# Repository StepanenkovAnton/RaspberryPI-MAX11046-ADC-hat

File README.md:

# RaspberryPI-MAX11046-ADC-hat
The Raspberry PI add-on boad with the 16 bit 6-channel ADC intended for 3 voltage + 3 current channels high-speed sampling in order to measure the power net
quality parameters like harmonics, power coefficient and so forth.

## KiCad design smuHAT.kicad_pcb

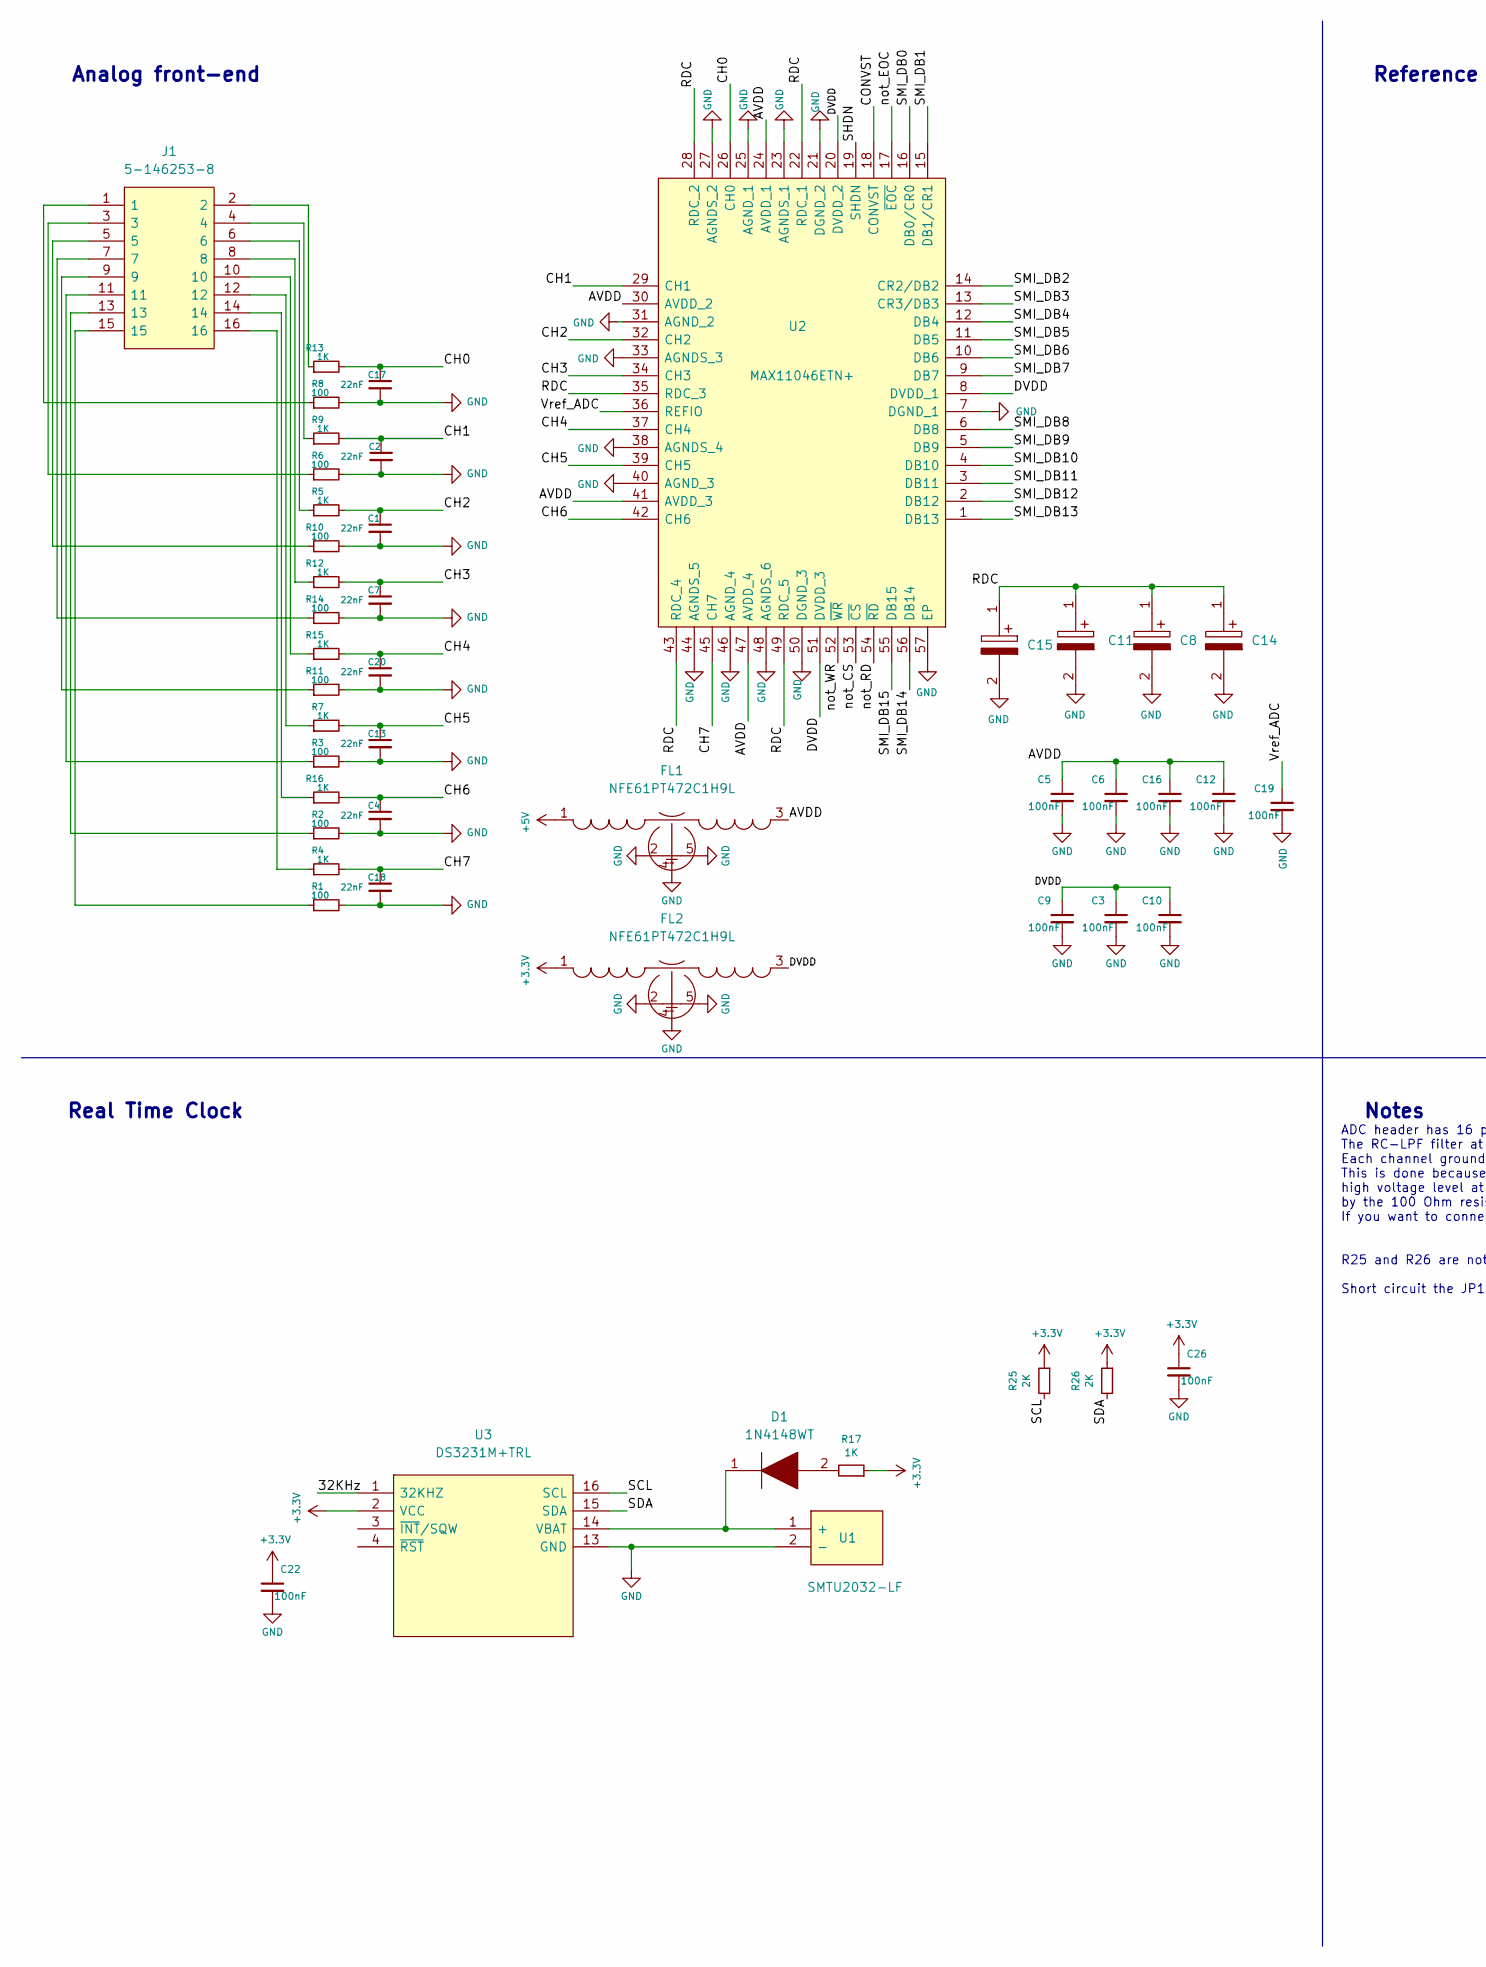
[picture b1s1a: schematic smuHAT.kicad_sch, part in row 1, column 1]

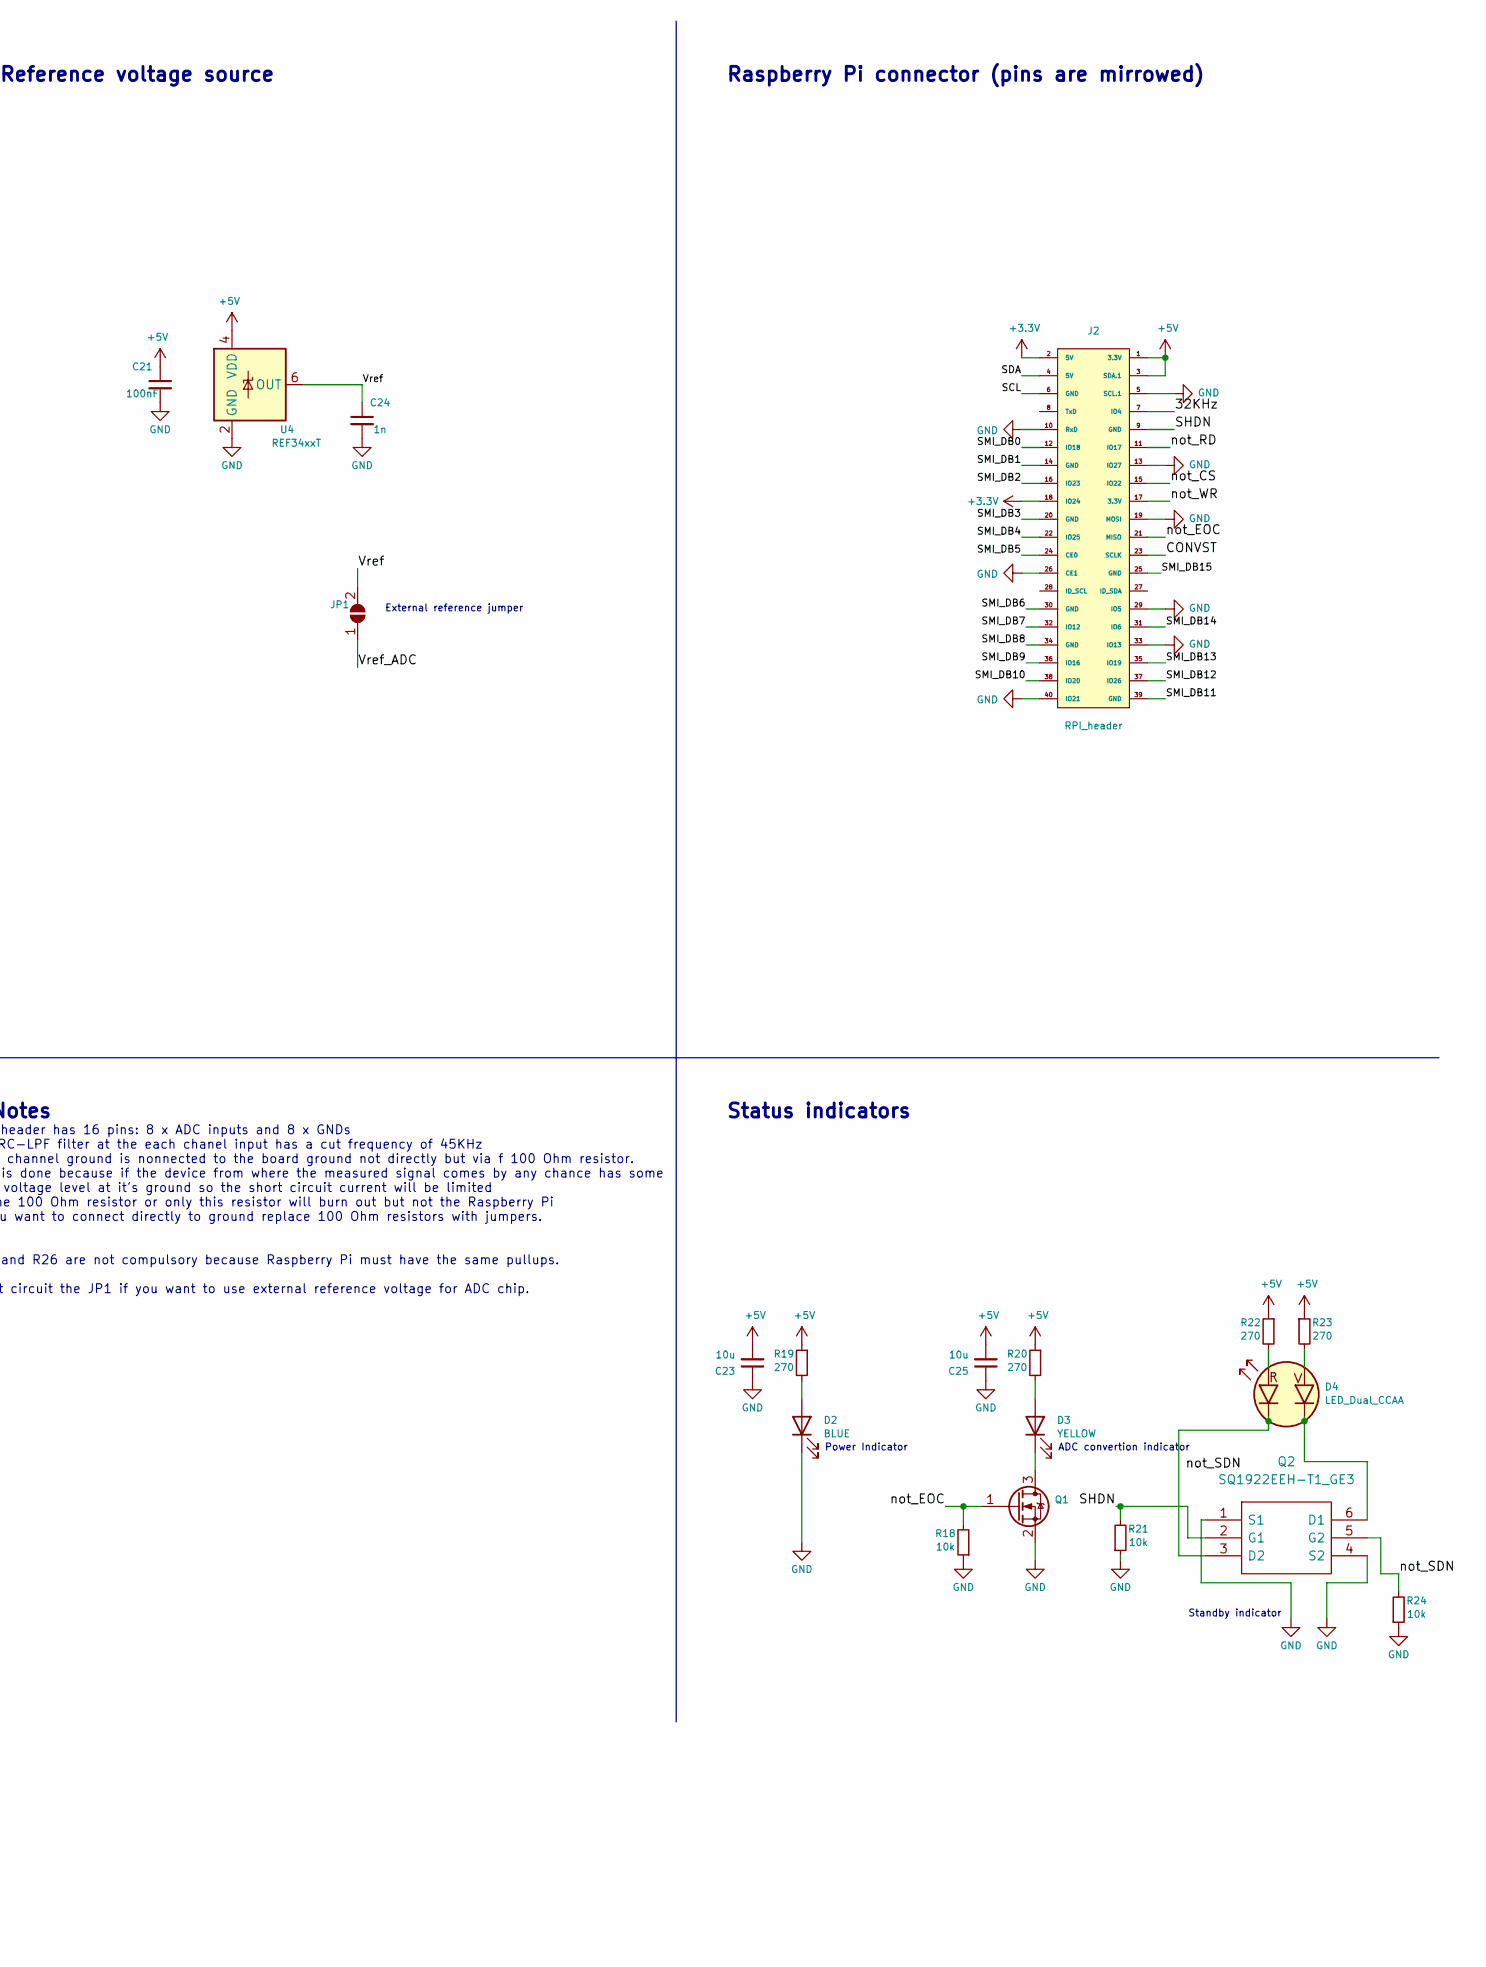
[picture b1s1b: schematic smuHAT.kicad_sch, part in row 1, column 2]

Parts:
C1, C2, C4, C7, C13, C17, C18, C20: 22nF; C_0603_1608Metric
C3, C5, C6, C9, C10, C12, C16, C19, C21, C22, C26: 100nF; C_0603_1608Metric
C8, C11, C14, C15: 33uF; CAPPM169X90N; Mouser Part Number 581-F981A336MMALZT
C23, C25: 10u; C_0603_1608Metric
C24: 1n; C_0603_1608Metric
D1: 1N4148WT; SODFL1608X70N; Mouser Part Number 512-1N4148WT
D2: BLUE; WL-SMCC
D3: YELLOW; WL-SMCC
D4: LED_Dual_CCAA; WL-SBCC
FL1, FL2: NFE61PT472C1H9L; NFE61; Mouser Part Number 81-NFE61PT472C1H9L
J1: 5-146253-8; HDRV16W68P254_2X8_1991X488X1045P; Mouser Part Number 571-5-146253-8
J2: RPI_header; PinSocket_2x20_P2.54mm_Vertical
JP1: External ref. voltage; SolderJumper-2_P1.1mm_Open_RoundedPad0.8x0.9mm
Q1: XP231N02013R; SOT-323_SC-70
Q2: SQ1922EEH-T1_GE3; SOT95P284X110-6N; Mouser Part Number 78-SQ1922EEH-T1_GE3
R1, R2, R3, R6, R8, R10, R11, R14: 100; R_0603_1608Metric
R4, R5, R7, R9, R12, R13, R15, R16, R17: 1K; R_0603_1608Metric
R18, R21, R24: 10k; R_0603_1608Metric
R19, R20, R22, R23: 270; R_0603_1608Metric
R25, R26: 2K; R_0603_1608Metric
U1: SMTU2032-LF; SMTU2032LF; Mouser Part Number 614-SMTU2032-LF
U2: MAX11046ETN+; QFN50P800X800X80-57N; Mouser Part Number 700-MAX11046ETN
U3: DS3231M+TRL; SOIC127P1032X265-16N; Mouser Part Number 700-DS3231M+TRL
U4: REF34xxT; SOT-23-6

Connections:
+3.3V: C22.1, C26.1, FL2.1, J2.2 (5V), J2.18 (IO24), R17.1, R25.1, R26.1, U3.2 (VCC)
+5V: C21.1, C23.2, C25.2, FL1.1, J2.1 (3.3V), J2.3 (SDA.1), R19.1, R20.1, R22.1, R23.1, U4.4 (VDD)
/32KHz: J2.7 (IO4), U3.1 (32KHZ)
/AVDD: C5.1, C6.1, C12.1, C16.1, FL1.3, U2.24 (AVDD_1), U2.30 (AVDD_2), U2.41 (AVDD_3), U2.47 (AVDD_4)
/CH0: C17.1, R13.2, U2.26 (CH0)
/CH1: C2.1, R9.2, U2.29 (CH1)
/CH2: C1.1, R5.2, U2.32 (CH2)
/CH3: C7.1, R12.2, U2.34 (CH3)
/CH4: C20.1, R15.2, U2.37 (CH4)
/CH5: C13.1, R7.2, U2.39 (CH5)
/CH6: C4.1, R16.2, U2.42 (CH6)
/CH7: C18.1, R4.2, U2.45 (CH7)
/CONVST: J2.23 (SCLK), U2.18 (CONVST)
/DVDD: C3.1, C9.1, C10.1, FL2.3, U2.8 (DVDD_1), U2.20 (DVDD_2), U2.51 (DVDD_3)
/RDC: C8.1, C11.1, C14.1, C15.1, U2.22 (RDC_1), U2.28 (RDC_2), U2.35 (RDC_3), U2.43 (RDC_4), U2.49 (RDC_5)
/SCL: J2.6 (GND), R25.2, U3.16 (SCL)
/SDA: J2.4 (5V), R26.2, U3.15 (SDA)
/SHDN: J2.9 (GND), Q2.2 (G1), R21.2, U2.19 (SHDN)
/SMI_DB0: J2.12 (IO18), U2.16 (DB0/CR0)
/SMI_DB1: J2.14 (GND), U2.15 (DB1/CR1)
/SMI_DB2: J2.16 (IO23), U2.14 (CR2/DB2)
/SMI_DB3: J2.20 (GND), U2.13 (CR3/DB3)
/SMI_DB4: J2.22 (IO25), U2.12 (DB4)
/SMI_DB5: J2.24 (CE0), U2.11 (DB5)
/SMI_DB6: J2.30 (GND), U2.10 (DB6)
/SMI_DB7: J2.32 (IO12), U2.9 (DB7)
/SMI_DB8: J2.34 (GND), U2.6 (DB8)
/SMI_DB9: J2.36 (IO16), U2.5 (DB9)
/SMI_DB10: J2.38 (IO20), U2.4 (DB10)
/SMI_DB11: J2.39 (GND), U2.3 (DB11)
/SMI_DB12: J2.37 (IO26), U2.2 (DB12)
/SMI_DB13: J2.35 (IO19), U2.1 (DB13)
/SMI_DB14: J2.31 (IO6), U2.56 (DB14)
/SMI_DB15: J2.25 (GND), U2.55 (DB15)
/Vref: C24.1, JP1.2 (B), U4.6 (OUT)
/Vref_ADC: C19.1, JP1.1 (A), U2.36 (REFIO)
/not_CS: J2.15 (IO22), U2.53 (~CS)
/not_EOC: J2.21 (MISO), Q1.1 (G), R18.2, U2.17 (~EOC)
/not_RD: J2.11 (IO17), U2.54 (~RD)
/not_SDN: Q2.5 (G2), R24.2
/not_WR: J2.17 (3.3V), U2.52 (~WR)
GND: C1.2, C2.2, C3.2, C4.2, C5.2, C6.2, C7.2, C8.2, C9.2, C10.2, C11.2, C12.2, C13.2, C14.2, C15.2, C16.2, C17.2, C18.2, C19.2, C20.2, C21.2, C22.2, C23.1, C24.2, C25.1, C26.2, D2.1 (K), FL1.2, FL1.4, FL1.5, FL2.2, FL2.4, FL2.5, J2.5 (SCL.1), J2.10 (RxD), J2.13 (IO27), J2.19 (MOSI), J2.26 (CE1), J2.29 (IO5), J2.33 (IO13), J2.40 (IO21), Q1.2 (S), Q2.1 (S1), Q2.4 (S2), R1.2, R2.2, R3.2, R6.2, R8.2, R10.2, R11.2, R14.2, R18.1, R21.1, R24.1, U1.2 (-), U2.7 (DGND_1), U2.21 (DGND_2), U2.23 (AGNDS_1), U2.25 (AGND_1), U2.27 (AGNDS_2), U2.31 (AGND_2), U2.33 (AGNDS_3), U2.38 (AGNDS_4), U2.40 (AGND_3), U2.44 (AGNDS_5), U2.46 (AGND_4), U2.48 (AGNDS_6), U2.50 (DGND_3), U2.57 (EP), U3.13 (GND), U4.2 (GND)
unnamed: D1.1, U1.1 (+), U3.14 (VBAT)
unnamed: D1.2, R17.2
unnamed: D2.2 (A), R19.2
unnamed: D3.1 (K), Q1.3 (D)
unnamed: D3.2 (A), R20.2
unnamed: J1.1, R8.1
unnamed: J1.2, R13.1
unnamed: J1.3, R6.1
unnamed: J1.4, R9.1
unnamed: J1.5, R10.1
unnamed: J1.6, R5.1
unnamed: J1.7, R14.1
unnamed: J1.8, R12.1
unnamed: J1.9, R11.1
unnamed: J1.10, R15.1
unnamed: J1.11, R3.1
unnamed: J1.12, R7.1
unnamed: J1.13, R2.1
unnamed: J1.14, R16.1
unnamed: J1.15, R1.1
unnamed: J1.16, R4.1
unnamed: D4.2 (K1), Q2.3 (D2)
unnamed: D4.1 (K2), Q2.6 (D1)
unnamed: D4.3 (A1), R22.2
unnamed: D4.4 (A2), R23.2

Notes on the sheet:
External reference jumper
Raspberry Pi connector (pins are mirrowed)
Real Time Clock
Standby indicator
Power Indicator
Status indicators
ADC convertion indicator
Reference voltage source
ADC header has 16 pins: 8 x ADC inputs and 8 x GNDs The RC-LPF filter at the each chanel input has a cut frequency of 45KHz Each channel ground is nonnected to the board ground not directly but via f 100 Ohm resistor. This is done because if the device from where the measured signal comes by any ch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
Notes
Analog front-end

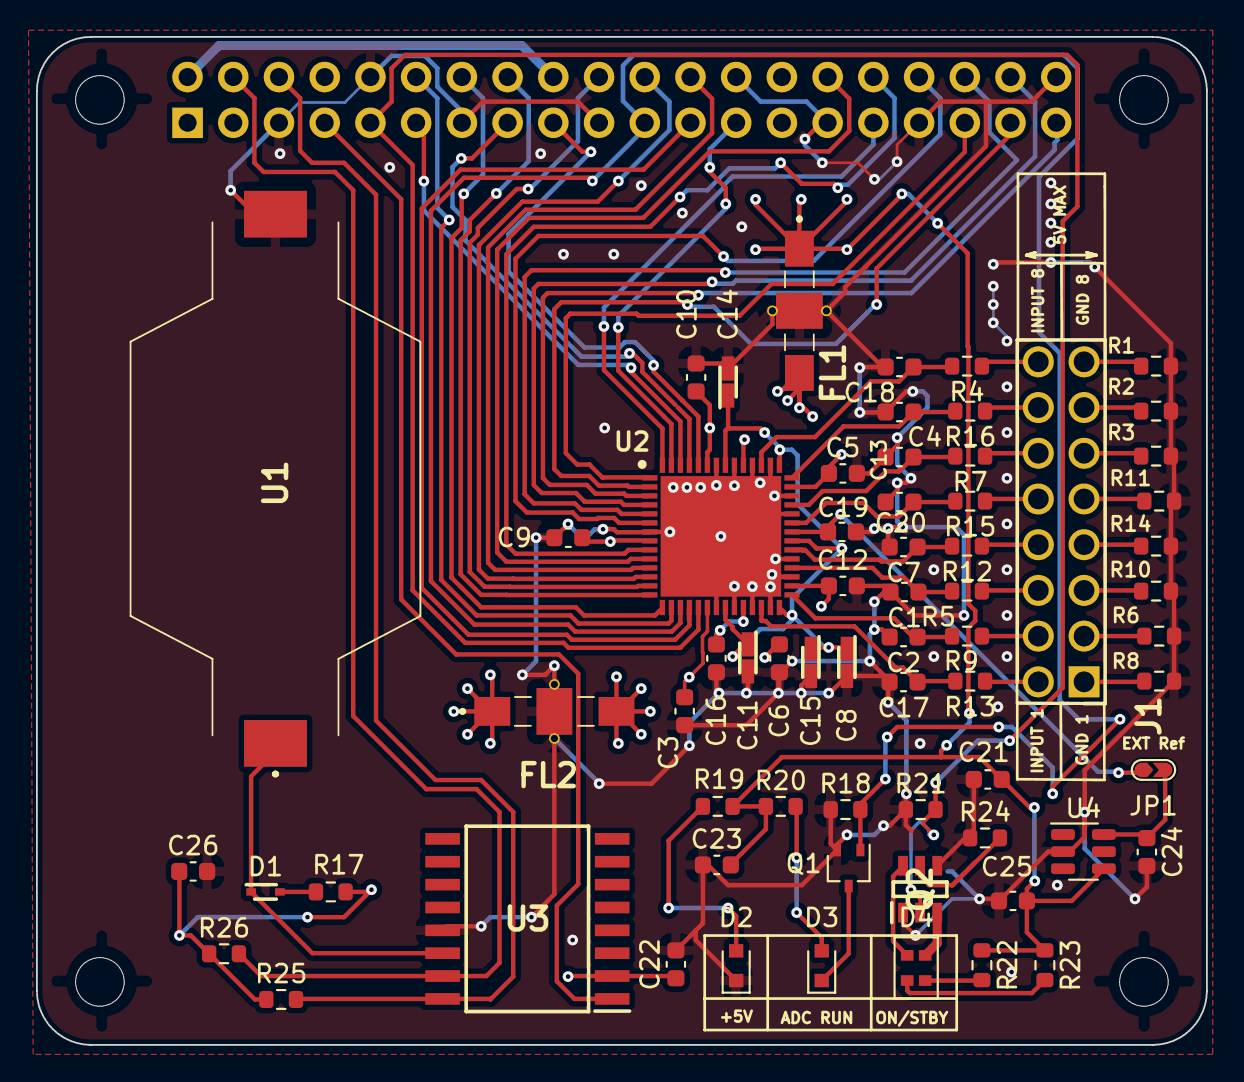
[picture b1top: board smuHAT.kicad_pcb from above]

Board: 4 copper layers, 65.0 x 56.0 mm, 67 parts (1 on the bottom side), 67 nets.

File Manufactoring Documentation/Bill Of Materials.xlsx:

Schematic Position | Value | Footprint | Datasheet | Description | Brand | Mfr. Part number | Qty | Price INR | Total
> C8, C11, C14, C15 | 33uF | smu:CAPPM169X90N | https://www.mouser.in/datasheet/2/40/AVX_F98_DTSH_08_16-1158749.pdf | CAPACITOR TANTALUM SOLID RESIN-MOLDED CHIP, HIGH CV UNDERTAB | KYOCERA AVX | F981A336MMALZT | 4 | 64.31 | 257.24
> C3, C5, C6, C9, C10, C12, C16, C19, C21, C22, C26 | 100nF | Capacitor_SMD:C_0603_1608Metric | https://www.mouser.in/datasheet/2/40/AutoMLCC-777028.pdf | Multilayer Ceramic Capacitors MLCC - SMD/SMT 50V 10pF C0G 0603 1% AEC-Q200 | KYOCERA AVX | 06035A100F4T4A | 11 | 35 | 385
> C1, C2, C4, C7, C13, C17, C18, C20 | 22nF | Capacitor_SMD:C_0603_1608Metric | https://www.mouser.in/datasheet/2/281/murata_03052018_GRM_Se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 | Multilayer Ceramic Capacitors MLCC - SMD/SMT 1500PF 50V 1% 0603 | Murata Electronics | GRM1885C1H152FA01D | 8 | 13.02 | 104.16
C24 | 1n | Capacitor_SMD:C_0603_1608Metric | https://product.tdk.com/system/files/dam/doc/product/capacit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 | Multilayer Ceramic Capacitors MLCC - SMD/SMT RECOMMENDED ALT 810-C0603X7R1E102K | TDK | C0603X7R1E102M030BA | 1 | 8.14 | 8.14
> C23, C25 | 10u | Capacitor_SMD:C_0603_1608Metric | https://www.mouser.in/datasheet/2/40/cx5r-776519.pdf | Multilayer Ceramic Capacitors MLCC - SMD/SMT 25V 10uF X5R 0603 20% | KYOCERA AVX | 06033D106MAT2A | 2 | 29.3 | 58.6
D1 | 1N4148WT | smu:SODFL1608X70N | https://componentsearchengine.com/Datasheets/2/1N4148WT.pdf | ON SEMICONDUCTOR - 1N4148WT - DIODE, SWITCHING, 75V, SOD-523F-2 | onsemi | 1N4148WT | 1 | 16.28 | 16.28
D2 | BLUE | smu:WL-SMCC | https://www.we-online.com/catalog/datasheet/150060BS73220.pdf |  | Wurth Elektronik | 150060BS73220 | 1 | 26.86 | 26.86
D3 | YELLOW | smu:WL-SMCC | https://www.we-online.com/catalog/datasheet/150060YS73220.pdf |  | Wurth Elektronik | 150060YS73220 | 1 | 26.86 | 26.86
D4 | LED_Dual_CCAA | smu:WL-SBCC | https://www.we-online.com/catalog/datasheet/150060RV75240.pdf |  | Wurth Elektronik | 150060RV75240 | 1 | 60.24 | 60.24
> FL1, FL2 | NFE61PT472C1H9L | smu:NFE61 | https://www.murata.com/en-us/products/productdetail?partno=N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 | SMT EMI filter capacitor,4700pF 50Vdc Murata NFE61HT / PT Series 2A 50 V dc SMD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 | Murata Electronics | NFE61PT472C1H9L | 2 | 63.49 | 126.98
J1 | 5-146253-8 | smu:HDRV16W68P254_2X8_1991X488X1045P | https://www.mouser.fr/datasheet/2/418/6/ENG_CD_146253_J3-200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 | 16 MODII HDR DRST B/A .100CL LF | TE Connectivity | 5-146253-8 | 1 | 346.76 | 346.76
J2 | RPI_header | Connector_PinSocket_2.54mm:PinSocket_2x20_P2.54mm_Vertical | https://suddendocs.samtec.com/catalog_english/ssq_th.pdf |  | Samtec | SSQ-120-01-F-D | 1 | 560.85 | 560.85
Q1 | XP231N02013R | Package_TO_SOT_SMD:SOT-323_SC-70 | https://eu.mouser.com/datasheet/2/760/TOSL_S_A0010841704_1-2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 | MOSFET N-CHANNEL 30V 0.2A |  | Torex Semiconductor | 1 | 28.49 | 28.49
Q2 | SQ1922EEH-T1_GE3 | Package_TO_SOT_SMD:SOT-353_SC-70-5 | https://www.mouser.com.tr/datasheet/2/427/sq1922eeh-1766298.pdf |  |  |  | 1 | 30 | 30
> R1-R3, R6, R8, R10, R11, R14 | 100 | Resistor_SMD:R_0603_1608Metric | https://www.mouser.in/datasheet/2/315/AOA0000C307-1149632.pdf | Thin Film Resistors - SMD 0603 536ohm 0.1% 25ppm | Panasonic | ERA-3AEB5360V | 8 | 28.49 | 227.92
> R4, R5, R7, R9, R12, R13, R15-R17 | 1K | Resistor_SMD:R_0603_1608Metric | https://www.mouser.in/datasheet/2/447/PYu_RC_Group_51_RoHS_L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 | Thick Film Resistors - SMD 1 kOhms 100mW 0603 1% | YAGEO | RC0603FR-071KL | 9 | 8.14 | 73.260000000000005
> R18, R21, R24 | 10k | Resistor_SMD:R_0603_1608Metric | https://www.mouser.in/datasheet/2/447/PYu_RC_Group_51_RoHS_L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 | Thick Film Resistors - SMD 10 kOhms 100mW 0603 1% | YAGEO | RC0603FR-0710KL | 3 | 8.14 | 24.42
> R19, R20, R22, R23 | 270 | Resistor_SMD:R_0603_1608Metric | https://www.mouser.in/datasheet/2/447/PYu_AR_51_RoHS_L_7-300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 | Thick Film Resistors - SMD 270Ohms 1/10W 0603 5% | YAGEO | AR0603JR-07270RL | 4 | 25.23 | 100.92
> R25, R26 | 2K | Resistor_SMD:R_0603_1608Metric | https://www.mouser.in/datasheet/2/351/Xicon_09112019_XC-6000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 | Thick Film Resistors - SMD 1/10WATT 2KOHMS 5% | Xicon | SDR03EZPD2001 | 2 | 10 | 20
U1 | SMTU2032-LF | smu:SMTU2032LF | https://www.mouser.com.tr/datasheet/2/427/sq1922eeh-1766298.pdf | Coin Cell Battery Holders SFC MNT FOR CR2032 | RENATA | SMTU2032-LF | 1 | 51.28 | 51.28
U2 | MAX11046ETN+ | smu:QFN50P800X800X80-57N | https://datasheet.datasheetarchive.com/originals/distributor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 | MAX11046ETN+, 16 bit ADC 8-channel, Parallel, 56-Pin TQFN | Maxim Integrated | MAX11046ETN+ | 1 | 2882.37 | 2882.37
U3 | DS3231M+TRL | smu:SOIC127P1032X265-16N | http://componentsearchengine.com/Datasheets/1/DS3231M+TRL.pdf | +/-5ppm, I2C Real-Time Clock | Maxim Integrated | DS3231M+TRL | 1 | 789 | 789
U4 | REF34xxT | Package_TO_SOT_SMD:SOT-23-6 | https://www.ti.com/lit/ds/symlink/ref3440.pdf |  |  | Substitute-REF3240AIDBVT | 1 | 602 | 602
 |  |  |  |  |  | REF3440TIDBVR |  | Total | 6807.63

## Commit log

2023-01-25 Custom libraries
2023-01-25 KiCAD Project
2023-01-25 Shematic diagram
2023-01-25 render

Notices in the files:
smuHAT.kicad_pcb:
License: Creative Commons Attribution 4.0 International License
